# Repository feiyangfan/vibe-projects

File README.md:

# vibe-projects
A collection of vibe-coded apps, utilities, and experiments.

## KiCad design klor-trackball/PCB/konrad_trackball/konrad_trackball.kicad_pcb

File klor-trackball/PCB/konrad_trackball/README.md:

# Konrad Trackball KiCad Derivative

This directory is the editable KiCad source for the KLOR 1.4 MX Konrad right-hand PMW3360 trackball derivative.

## Task 3A baseline

Task 3A creates this project as a non-destructive fork of the stock KLOR 1.4 KiCad project.

Baseline rules:

- Stock source remains under `klor-trackball/klor1.4/PCB/klor1_4/` and must not be edited.
- The derivative project basename is `konrad_trackball`.
- `konrad_trackball.kicad_pcb` and `konrad_trackball.kicad_sch` begin byte-identical to the stock `klor1_4` board and schematic.
- The stock design-rules file and local KLOR symbol/footprint libraries are copied unchanged.
- The only intentional content difference in the baseline project file is `meta.filename`, changed from `klor1_4.kicad_pro` to `konrad_trackball.kicad_pro`.
- Stock Gerbers are intentionally not copied. Fabrication outputs must be regenerated from the completed derivative later.
- No Task 2 electrical changes are implemented in Task 3A. Those begin with Task 3B.

Canonical Task 3 plan and gates are documented in `../../design/task3/README.md`.

## Task 3B schematic contract

Task 3B is complete.

The derivative schematic now owns the frozen Task 2 electrical interface:

- `SW22` and `D22` are removed from the schematic;
- RGB is bypassed logically as `SW13 DOUT → SW14 DIN`;
- U1-side nets are `PMW_SCK`, `PMW_MOSI`, `PMW_MISO`, and `PMW_CS`;
- `J4` is the 1×7 PMW3360/Kivipallur keyboard-side connector:
  `1=PMW_CS, 2=PMW_MISO, 3=PMW_MOSI, 4=PMW_SCK, 5=NC, 6=VCC, 7=GND`;
- `J1.3` is NC and `J1.4/TX` remains the active split connection;
- `J2`, `OLED1`, and `BZ1` are DNP for revision 1.

The PCB remained the stock baseline through Task 3B. Task 3C subsequently synchronized the physical board.

See `../../design/task3/TASK3B_RESULT.md`.

## Task 3C PCB synchronization

Task 3C is complete.

The PCB now matches the authorized destructive portion of the Task 3B contract:

- `SW22` and `D22` are physically removed;
- the deleted-key local matrix copper is removed while `col1` and `row3` remain distinct;
- `RX` is retired and `J1.3` is physically no-net;
- `J1.4/TX` remains intact;
- U1 owns `PMW_SCK`, `PMW_MOSI`, `PMW_MISO`, and `PMW_CS`;
- SW13 DOUT and SW14 DIN are one PCB net with a permanent B.Cu splice;
- J4 exists with the frozen 1×7 keyboard-side pin contract.

Task 3C left J4 staged off-board and kept stock Edge.Cuts unchanged.

See `../../design/task3/TASK3C_RESULT.md`.

## Task 3D connector and pass-through

Task 3D is complete.

- J4 is final-placed on `F.Cu` at `(147.724665,142.367997)`, rotation 0°.
- Its row midpoint is `(147.724665,134.747997)`, +4.613622 mm X from the locked breakout guide center.
- The board has an actual open 2 mm edge notch matching the locked 2×22 mm service envelope.
- A local +X tongue supports the J4 through-holes.
- VCC and the RGB bypass are locally rerouted only where required by the notch/header.
- At the end of Task 3D, J4-to-U1 PMW routing was intentionally incomplete; Task 3E completes it below.

See `../../design/task3/TASK3D_RESULT.md`.

## Task 3E PMW3360 routing

Task 3E is complete.

- `PMW_CS`, `PMW_MISO`, `PMW_MOSI`, and `PMW_SCK` are routed from U1 to J4.
- J4.6 connects to the existing `VCC` rail.
- J4.7 connects to `GND`.
- J4.5 / MOTION remains NC.
- The routing is additive; Task 3D connector/pass-through geometry and all pre-existing copper are preserved.

See `../../design/task3/TASK3E_RESULT.md`.

**Next: Task 3F — preservation and integrated DRC audit.**

## Zone-fill cache policy

Generated `filled_polygon` cache data is not committed. The Task 3E board remains directly accessible through repository tooling. Refill zones in KiCad before DRC/fabrication, then strip cached fills again before committing.

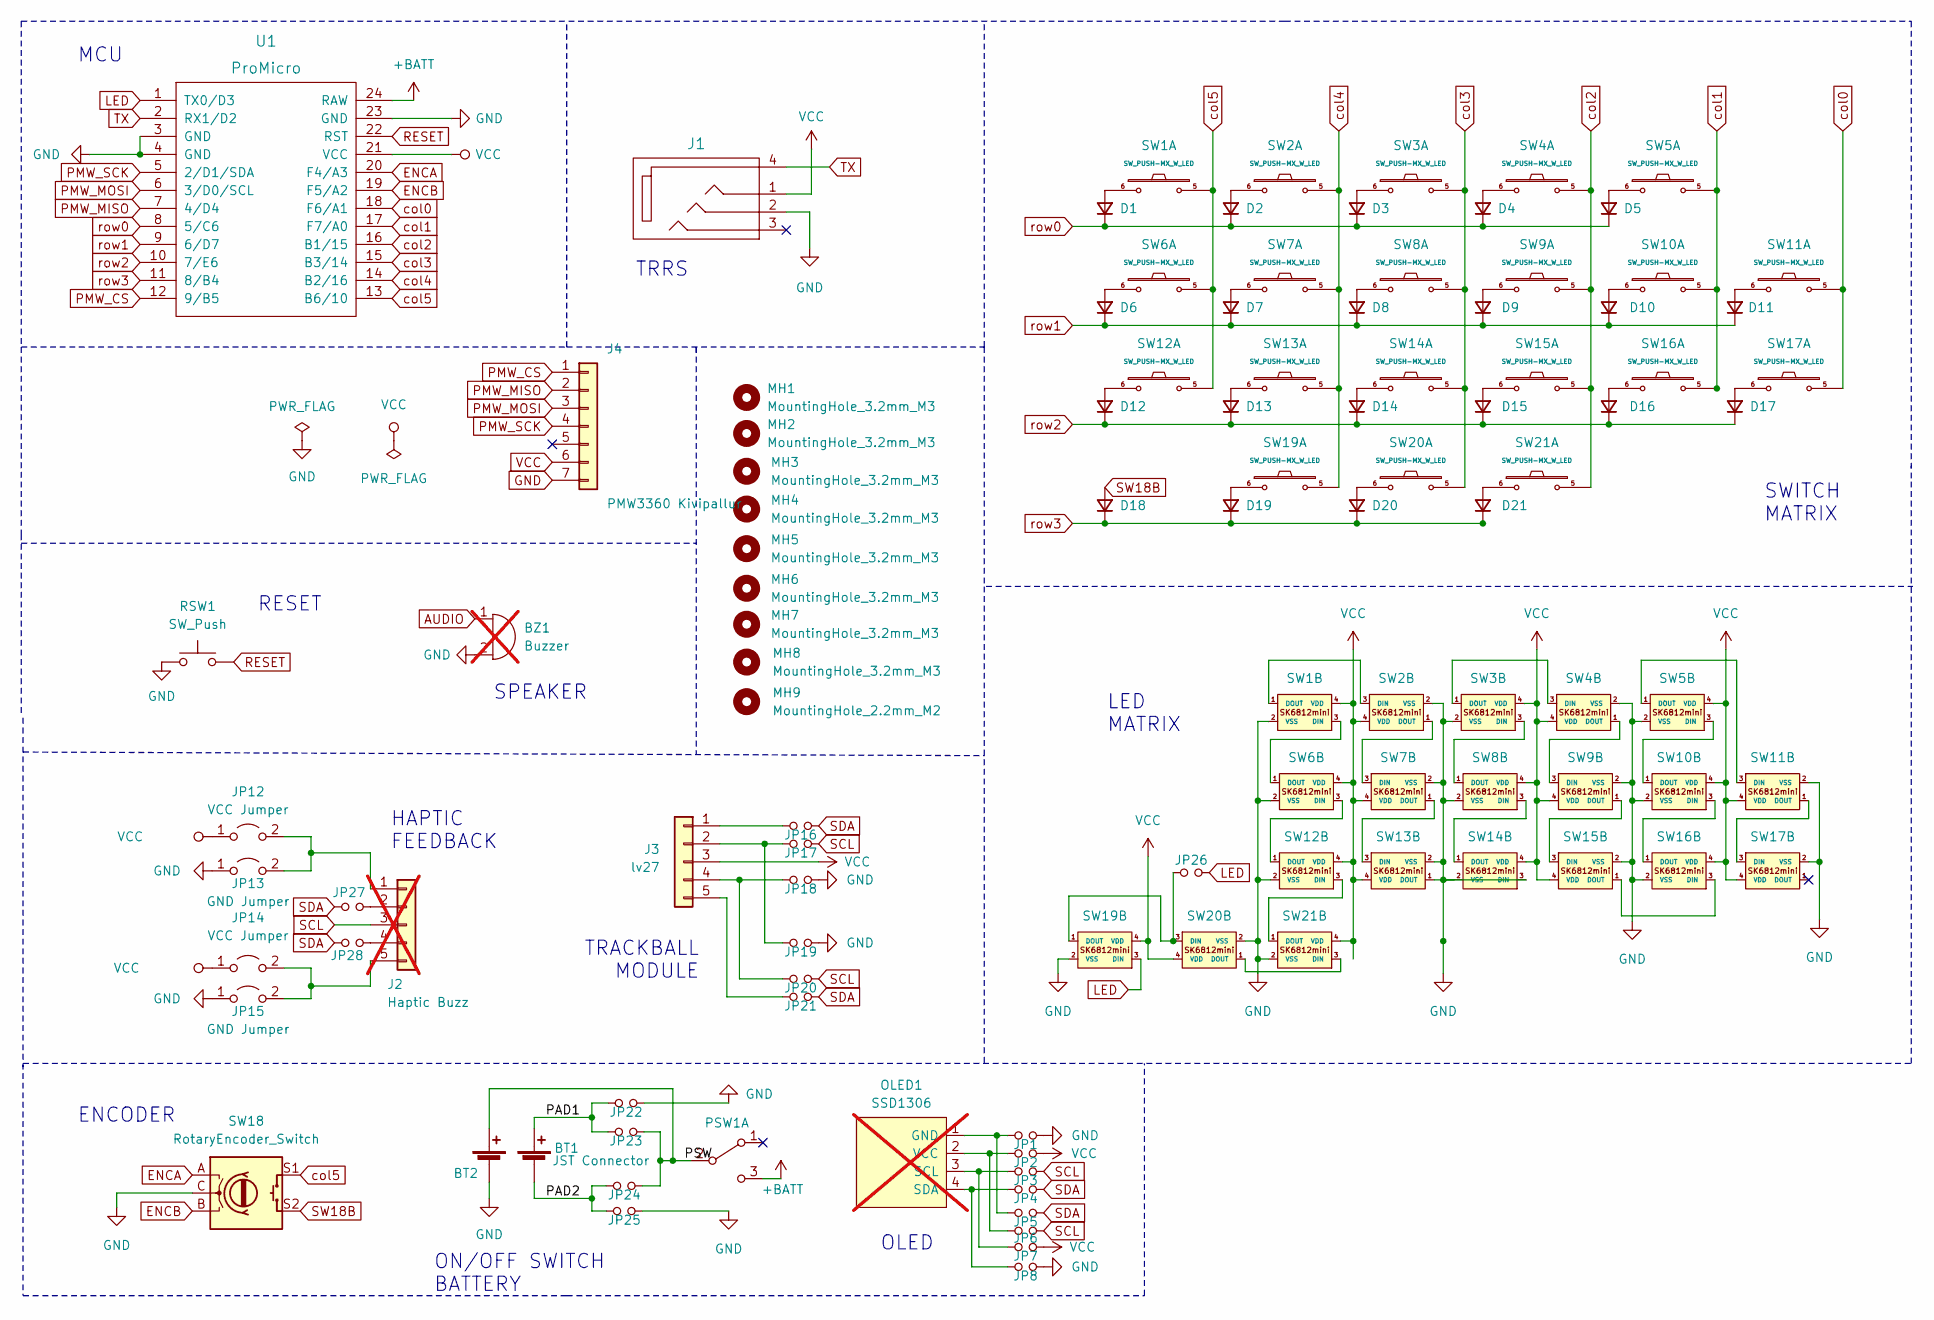
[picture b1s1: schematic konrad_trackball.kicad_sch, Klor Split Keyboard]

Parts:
BT1: JST Connector; JST_PH_reversible
BT2: Battery_Cell; custombatteryconnector_small
BZ1: Buzzer; Buzzer_Mallory_AST1109MLTRQ_reversible; not fitted
D1, D2, D3, D4, D5, D6, D7, D8, D9, D10, D11, D12, D13, D14, D15, D16, D17, D18, D19, D20, D21: D_Small; Diode_SOD123
J1: MJ-4PP-9
J2: Haptic Buzz; Pimoroni Haptic Buzz DRV2605L Driver; not fitted
J3: lv27; lvc27_onlyInput
J4: PMW3360 Kivipallur; PinHeader_1x07_P2.54mm_Vertical
JP1, JP2, JP3, JP4, JP5, JP6, JP7, JP8, JP16, JP17, JP18, JP19, JP20, JP21, JP22, JP23, JP24, JP25, JP26, JP27, JP28: Device_Jumper_NO_Small; Jumper
JP12, JP14: VCC Jumper; Jumper
JP13, JP15: GND Jumper; Jumper
MH1, MH2, MH3, MH4, MH5, MH6, MH7, MH8: MountingHole_3.2mm_M3
MH9: MountingHole_2.2mm_M2
OLED1: SSD1306; SSD1306_128x64OLED; not fitted
PSW1: SW_DPDT_x2; MSK12C02_reversible
RSW1: SW_Push; SW_Push_1P1T-MP_NO_Horizontal_Alps_SKRTLAE010_both_sides
SW1, SW2, SW3, SW4, SW5, SW6, SW7, SW8, SW9, SW10, SW11, SW12, SW13, SW14, SW15, SW16, SW17, SW19, SW20, SW21: SW_PUSH-MX_W_LED; SK6812MINI_and_cherry_1
SW18: RotaryEncoder_Switch; RotaryEncoder_Alps_EC11E-Switch_Vertical_H20mm-keebio_modif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
U1: ProMicro

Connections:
+BATT: PSW1.3 (C), U1.24 (RAW)
/PAD1: BT1.1 (+), JP22.1, JP23.1
/PAD2: BT1.2 (-), JP24.1, JP25.1
/PSW: BT2.1 (+), JP23.2, JP24.2, PSW1.2 (B)
AUDIO: BZ1.1 (-)
ENCA: SW18.A, U1.20 (F4/A3)
ENCB: SW18.B, U1.19 (F5/A2)
LED: JP26.2, SW19.3 (DIN), U1.1 (TX0/D3)
unnamed: D1.2 (A), SW1.6
unnamed: D2.2 (A), SW2.6
unnamed: D3.2 (A), SW3.6
unnamed: D4.2 (A), SW4.6
unnamed: D5.2 (A), SW5.6
unnamed: D6.2 (A), SW6.6
unnamed: D7.2 (A), SW7.6
unnamed: D8.2 (A), SW8.6
unnamed: D9.2 (A), SW9.6
unnamed: D10.2 (A), SW10.6
unnamed: D11.2 (A), SW11.6
unnamed: D12.2 (A), SW12.6
unnamed: D13.2 (A), SW13.6
unnamed: D14.2 (A), SW14.6
unnamed: D15.2 (A), SW15.6
unnamed: D16.2 (A), SW16.6
unnamed: D17.2 (A), SW17.6
unnamed: D19.2 (A), SW19.6
unnamed: D20.2 (A), SW20.6
unnamed: D21.2 (A), SW21.6
unnamed: J2.1, JP12.2 (B), JP13.2 (B)
unnamed: J2.2, JP27.2
unnamed: J2.4, JP28.2
unnamed: J2.5, JP14.2 (B), JP15.2 (B)
unnamed: J3.1, JP16.1
unnamed: J3.2, JP17.1, JP19.1
unnamed: J3.4, JP18.1, JP20.1
unnamed: J3.5, JP21.1
unnamed: JP1.1, JP5.1, OLED1.1 (GND)
unnamed: JP3.1, JP7.1, OLED1.3 (SCL)
unnamed: JP4.1, JP8.1, OLED1.4 (SDA)
unnamed: JP2.1, JP6.1, OLED1.2 (VCC)
unnamed: SW1.3 (DIN), SW6.1 (DOUT)
unnamed: SW1.1 (DOUT), SW2.3 (DIN)
unnamed: SW2.1 (DOUT), SW7.3 (DIN)
unnamed: SW3.3 (DIN), SW8.1 (DOUT)
unnamed: SW3.1 (DOUT), SW4.3 (DIN)
unnamed: SW4.1 (DOUT), SW9.3 (DIN)
unnamed: SW10.3 (DIN), SW16.1 (DOUT)
unnamed: SW5.3 (DIN), SW10.1 (DOUT)
unnamed: SW5.1 (DOUT), SW11.3 (DIN)
unnamed: SW11.1 (DOUT), SW17.3 (DIN)
unnamed: SW12.3 (DIN), SW21.1 (DOUT)
unnamed: SW6.3 (DIN), SW12.1 (DOUT)
unnamed: SW7.1 (DOUT), SW13.3 (DIN)
unnamed: SW8.3 (DIN), SW14.1 (DOUT)
unnamed: SW9.1 (DOUT), SW15.3 (DIN)
unnamed: SW15.1 (DOUT), SW16.3 (DIN)
unnamed: JP26.1, SW19.1 (DOUT), SW20.3 (DIN)
unnamed: SW20.1 (DOUT), SW21.3 (DIN)
PMW_CS: J4.1, U1.12 (9/B5)
PMW_MISO: J4.2, U1.7 (4/D4)
PMW_MOSI: J4.3, U1.6 (3/D0/SCL)
PMW_SCK: J4.4, U1.5 (2/D1/SDA)
RESET: RSW1.2, U1.22 (RST)
SCL: J2.3, JP3.2, JP6.2, JP17.2, JP20.2
SDA: JP4.2, JP5.2, JP16.2, JP21.2, JP27.1, JP28.1
SW18B: D18.2 (A), SW18.S2
TX: J1.4, U1.2 (RX1/D2)
VCC: J1.1, J3.3, J4.6, JP2.2, JP7.2, JP12.1 (A), JP14.1 (A), SW1.4 (VDD), SW2.4 (VDD), SW3.4 (VDD), SW4.4 (VDD), SW5.4 (VDD), SW6.4 (VDD), SW7.4 (VDD), SW8.4 (VDD), SW9.4 (VDD), SW10.4 (VDD), SW11.4 (VDD), SW12.4 (VDD), SW13.4 (VDD), SW14.4 (VDD), SW15.4 (VDD), SW16.4 (VDD), SW17.4 (VDD), SW19.4 (VDD), SW20.4 (VDD), SW21.4 (VDD), U1.21 (VCC)
col0: SW11.5, SW17.5, U1.18 (F6/A1)
col1: SW5.5, SW10.5, SW16.5, U1.17 (F7/A0)
col2: SW4.5, SW9.5, SW15.5, SW21.5, U1.16 (B1/15)
col3: SW3.5, SW8.5, SW14.5, SW20.5, U1.15 (B3/14)
col4: SW2.5, SW7.5, SW13.5, SW19.5, U1.14 (B2/16)
col5: SW1.5, SW6.5, SW12.5, SW18.S1, U1.13 (B6/10)
row0: D1.1 (K), D2.1 (K), D3.1 (K), D4.1 (K), D5.1 (K), U1.8 (5/C6)
row1: D6.1 (K), D7.1 (K), D8.1 (K), D9.1 (K), D10.1 (K), D11.1 (K), U1.9 (6/D7)
row2: D12.1 (K), D13.1 (K), D14.1 (K), D15.1 (K), D16.1 (K), D17.1 (K), U1.10 (7/E6)
row3: D18.1 (K), D19.1 (K), D20.1 (K), D21.1 (K), U1.11 (8/B4)

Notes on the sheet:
SWITCH MATRIX
MCU
ON/OFF SWITCH BATTERY
HAPTIC FEEDBACK
ENCODER
OLED
LED MATRIX
TRRS
TRACKBALL MODULE
RESET
SPEAKER

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
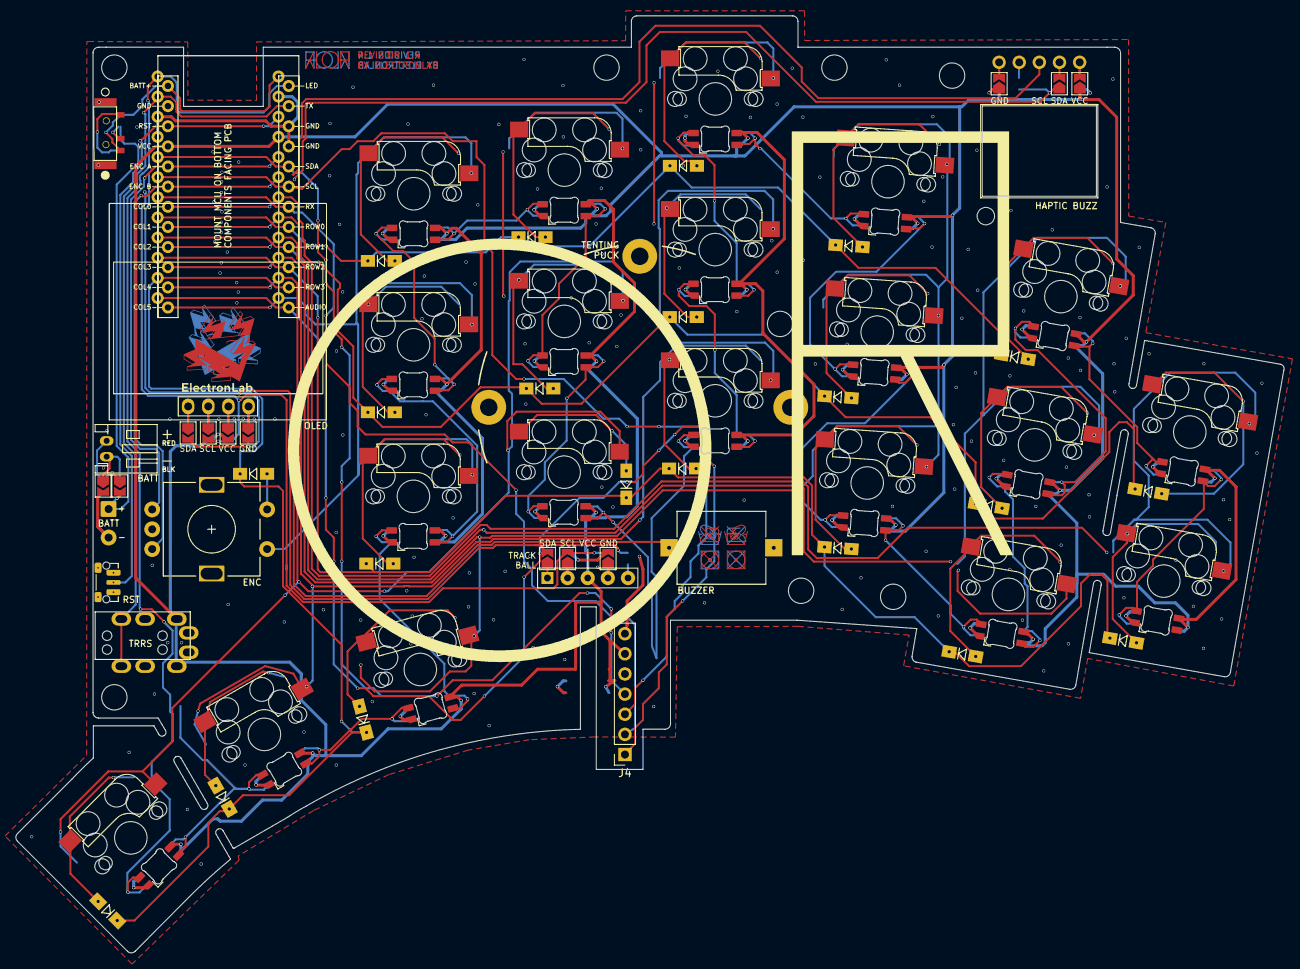
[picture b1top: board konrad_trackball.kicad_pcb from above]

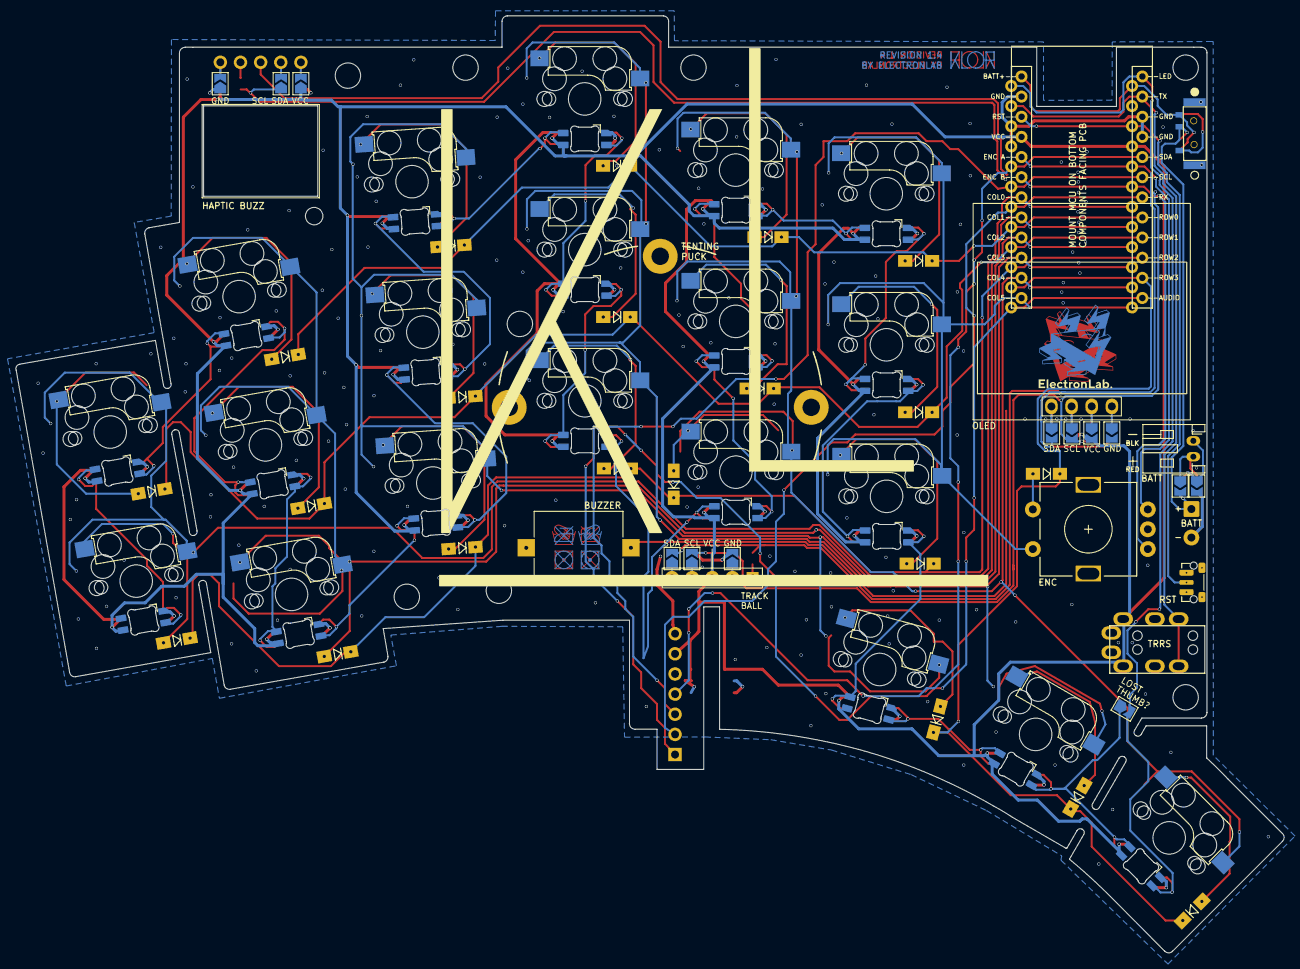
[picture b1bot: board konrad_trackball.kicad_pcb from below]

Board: 2 copper layers, 160.0 x 118.2 mm, 87 parts (14 on the bottom side), 79 nets.

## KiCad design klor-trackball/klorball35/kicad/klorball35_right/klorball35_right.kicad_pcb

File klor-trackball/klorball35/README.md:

# KLORBALL35

<picture>
  <source media="(prefers-color-scheme: dark)" srcset="/docs/images/klorball35-layout-dark.svg">
  <source media="(prefers-color-scheme: light)" srcset="/docs/images/klorball35-layout-light.svg">
  
</picture>

**Klorball35** is a 35-key, column-staggered, low-profile split keyboard with an integrated optical trackball. It's derived from [KLOR](https://github.com/GEIGEIGEIST/KLOR) and [Keyball](https://github.com/Yowkees/keyball),  built with [Kivipallur](https://github.com/dr3san/Kivipallur) as a starting point in [Ergogen](https://ergogen.cache.works/), and designed around Kailh Choc V1 switches, an [0xCB Helios](https://github.com/0xCB-dev/0xCB-Helios) (RP2040) controller per half, and a PixArt **PMW3360** sensor on the right hand.

***

## LAYOUT

Each half carries a 5-column × 3-row main matrix plus a 3-key (left) and 2-key (right)thumb cluster. The right hand gives up one key to make room for the trackball, so the two halves are **18 (left) + 17 (right) = 35 keys**.

- Column-staggered, splayed columns with per-column stagger/splay tuning
- Kailh Choc V1 (low-profile) switches, 18 × 17 mm spacing
- TRRS jack for the inter-half connection
- M2 mounting holes and a matching FR4 switchplate per half
- PMW3360 optical trackball on the right half via the *Kivipallur* breakout

***

## IMAGES

▲ The assembled Klorball35.

▲ Mounted on a tripod.

▲ The right-half trackball assembly.

***

## PCB

[`kicad/`](/kicad/) holds the KiCad 9 projects:

| Project | Description |
| --- | --- |
| [`klorball35_left`](/kicad/klorball35_left/) | Left-half PCB + schematic |
| [`klorball35_right`](/kicad/klorball35_right/) | Right-half PCB + schematic (trackball) |
| [`klorball35_plate_left`](/kicad/klorball35_plate_left/) | Left FR4 switchplate |
| [`klorball35_plate_right`](/kicad/klorball35_plate_right/) | Right FR4 switchplate |
| [`Kivipallur_PMW3360_breakout`](/kicad/Kivipallur_PMW3360_breakout/) | PMW3360 trackball sensor breakout |

Shared footprint and symbol libraries (`Keebio-Parts.pretty`, `keyswitches.pretty`, `Helios.pretty`, `Mounting_Hole.pretty`, etc.) live alongside the projects.

Manufacturing **Gerbers** are in [`gerbers/`](/gerbers/):

- `GERBER-klorball35_left.zip` / `GERBER-klorball35_right.zip` — main PCBs
- `GERBER-klorball35_plate_left.zip` / `GERBER-klorball35_plate_right.zip` — FR4 switchplates
- `GERBER-Kivipallur_PMW3360_breakout.zip` (+ BOM and CPL CSVs) — trackball breakout

***

## SOURCE

The whole board is generated from a single Ergogen definition, [`config.yml`](/config.yml) (Ergogen `4.2.1`). Regenerate the outlines and PCB scaffolds with:

```sh
ergogen config.yml --svg -o output
```

Outputs land in [`output/`](/output/) (`outlines/` as DXF/SVG and `pcbs/` as KiCad files), which are then finished by hand in KiCad.

***

## SWITCHPLATE

A matching FR4 switchplate is generated for each half (`klorball35_plate_left` / `klorball35_plate_right`, with Gerbers in `gerbers/`). The plate outline is shared with the main board; only the key cutouts and M2 screw holes differ.

***

## TRACKBALL

The right half integrates a PixArt **PMW3360DM-T2QU** optical sensor on the *Kivipallur* breakout ([`kicad/Kivipallur_PMW3360_breakout`](/kicad/Kivipallur_PMW3360_breakout/)). It connects to the right-hand Helios over SPI through the breakout slot in the PCB.

***

## FIRMWARE

Each half runs on an [0xCB Helios](https://github.com/0xCB-dev/0xCB-Helios) RP2040 controller (Pro Micro-compatible footprint), so the board can run **QMK** or **ZMK**. A dedicated Klorball35 firmware config isn't published yet; the stock [KLOR QMK config](https://github.com/GEIGEIGEIST/qmk-config-klor) and [KLOR ZMK config](https://github.com/GEIGEIGEIST/zmk-config-klor) are good starting points, with the matrix and the PMW3360 trackball wired up to match this board.

***

## CREDITS

- **[KLOR](https://github.com/GEIGEIGEIST/KLOR)** by [GEIGEIGEIST](https://github.com/GEIGEIGEIST) — One of the best keyboards I have used.
- **[0xCB Helios](https://github.com/0xCB-dev/0xCB-Helios)** by [0xCB](https://github.com/0xCB-dev) — the RP2040 controller.
- **[Ergogen](https://github.com/ergogen/ergogen)** by [MrZealot](https://github.com/mrzealot) — the keyboard generator.
- **[Kivipallur](https://github.com/dr3san/Kivipallur)** by [dr3san](https://github.com/dr3san) — the board that got this project started.
- **[25mm Trackball Housing](https://www.thingiverse.com/thing:6719828)** by [kepeo](https://www.thingiverse.com/kepeo/designs)
- The **Keebio** footprint library and the PixArt PMW3360 breakout that the Kivipallur design is based on.

Built by **danbowles**.

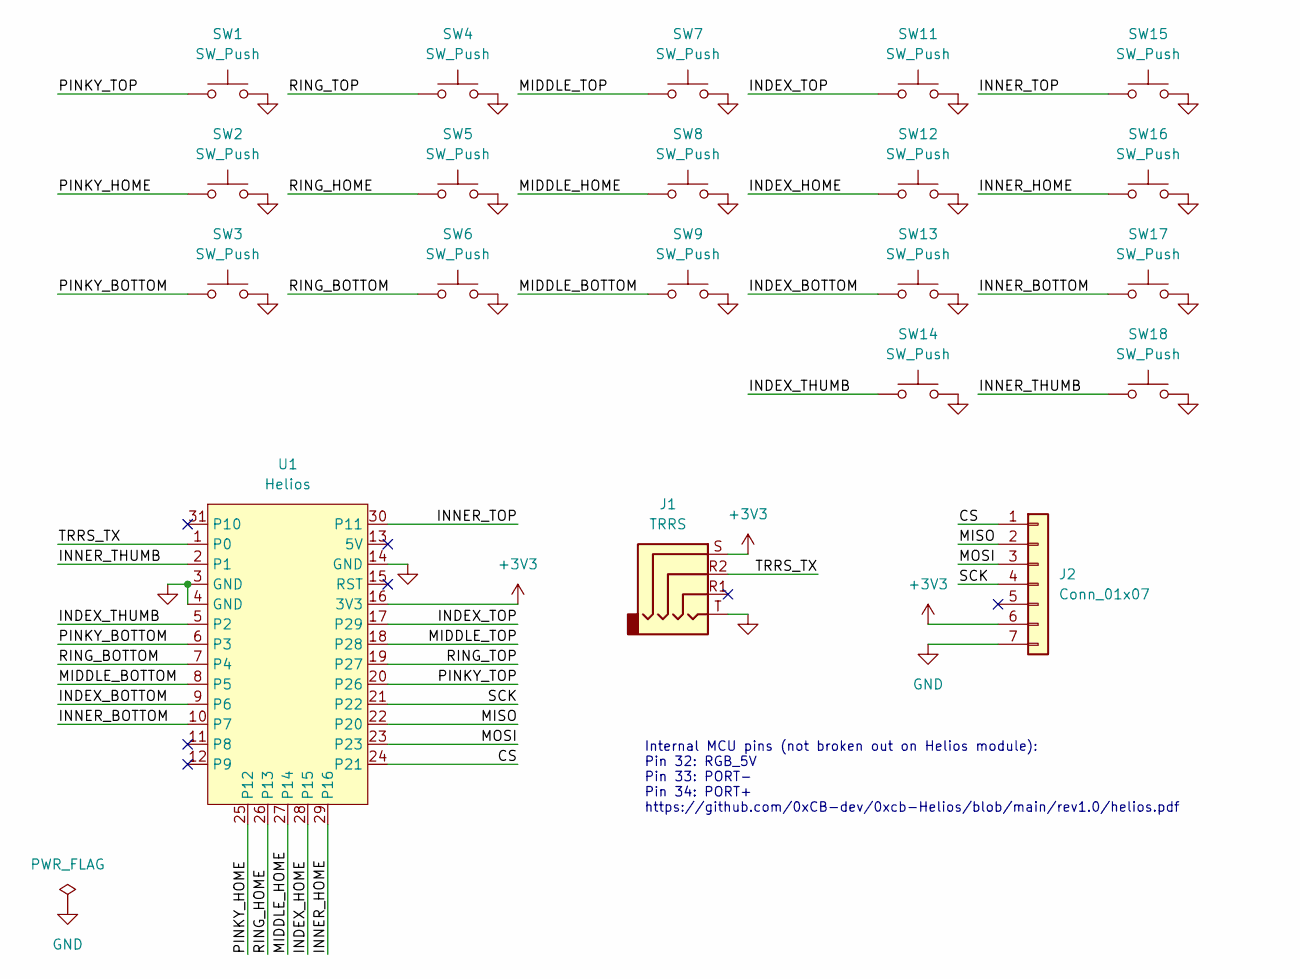
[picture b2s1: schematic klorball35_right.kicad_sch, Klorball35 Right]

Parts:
J1: TRRS; TRRS-PJ-320A
J2: Conn_01x07; PinHeader_1x07_P2.54mm_Vertical
SW1, SW2, SW3, SW4, SW5, SW6, SW7, SW8, SW9, SW11, SW12, SW13, SW14, SW15, SW16, SW17, SW18: SW_Push; Kailh_socket_PG1350_optional
U1: Helios; Helios_ACH

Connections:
+3V3: J1.S, J2.6, U1.16 (3V3)
/CS: J2.1, U1.24 (P21)
/INDEX_BOTTOM: SW13.1, U1.9 (P6)
/INDEX_HOME: SW12.1, U1.28 (P15)
/INDEX_THUMB: SW14.1, U1.5 (P2)
/INDEX_TOP: SW11.1, U1.17 (P29)
/INNER_BOTTOM: SW17.1, U1.10 (P7)
/INNER_HOME: SW16.1, U1.29 (P16)
/INNER_THUMB: SW18.1, U1.2 (P1)
/INNER_TOP: SW15.1, U1.30 (P11)
/MIDDLE_BOTTOM: SW9.1, U1.8 (P5)
/MIDDLE_HOME: SW8.1, U1.27 (P14)
/MIDDLE_TOP: SW7.1, U1.18 (P28)
/MISO: J2.2, U1.22 (P20)
/MOSI: J2.3, U1.23
/PINKY_BOTTOM: SW3.1, U1.6 (P3)
/PINKY_HOME: SW2.1, U1.25 (P12)
/PINKY_TOP: SW1.1, U1.20 (P26)
/RING_BOTTOM: SW6.1, U1.7 (P4)
/RING_HOME: SW5.1, U1.26 (P13)
/RING_TOP: SW4.1, U1.19 (P27)
/SCK: J2.4, U1.21 (P22)
/TRRS_TX: J1.R2, U1.1 (P0)
GND: J1.T, J2.7, SW1.2, SW2.2, SW3.2, SW4.2, SW5.2, SW6.2, SW7.2, SW8.2, SW9.2, SW11.2, SW12.2, SW13.2, SW14.2, SW15.2, SW16.2, SW17.2, SW18.2, U1.3 (GND), U1.4 (GND), U1.14 (GND)

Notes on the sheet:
Internal MCU pins (not broken out on Helios module): Pin 32: RGB_5V Pin 33: PORT- Pin 34: PORT+ https://github.com/0xCB-dev/0xcb-Helios/blob/main/rev1.0/helios.pdf

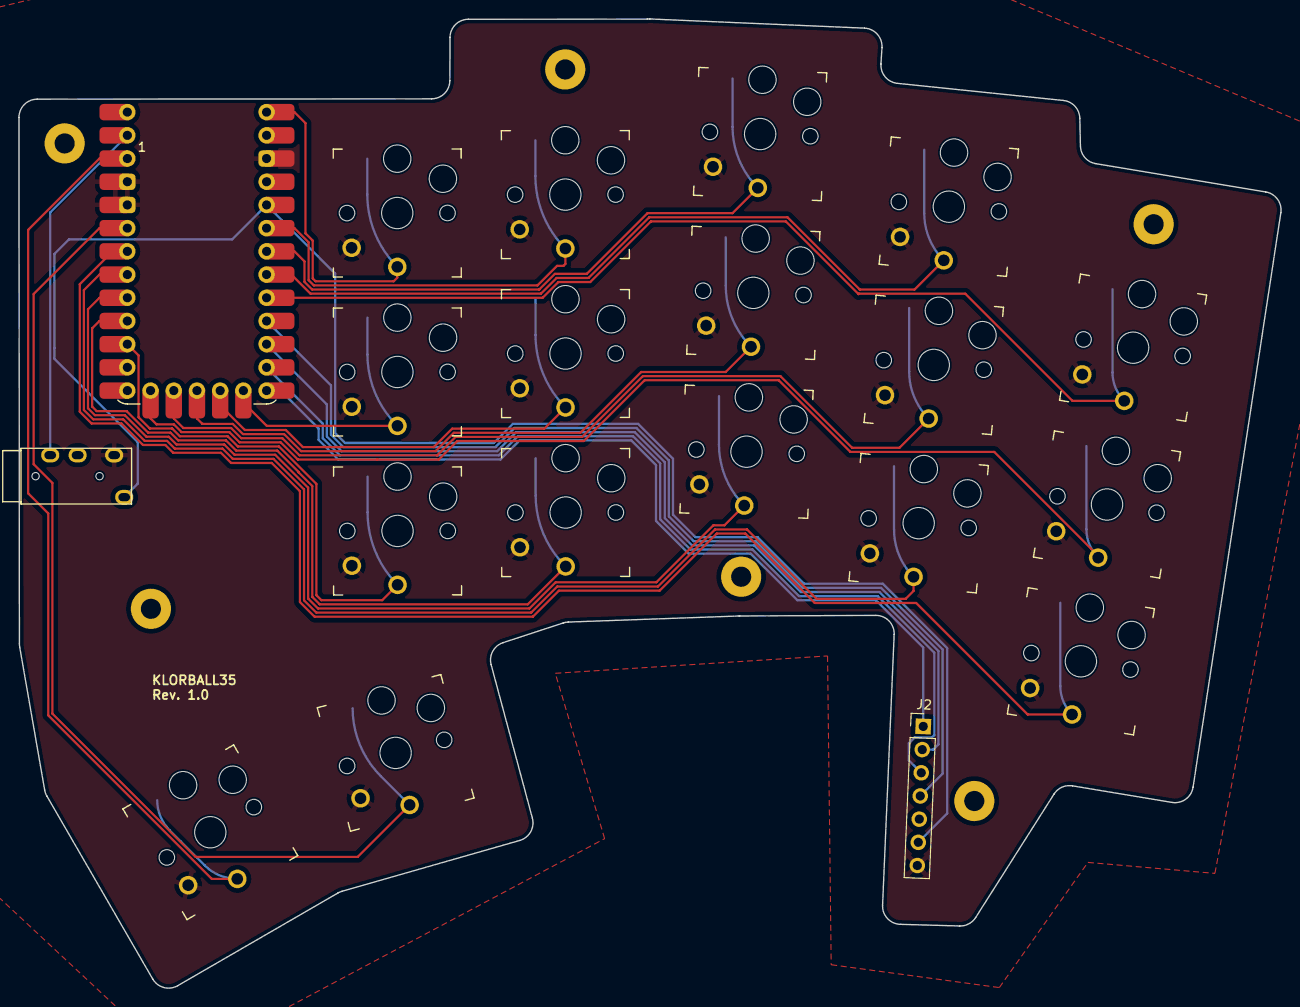
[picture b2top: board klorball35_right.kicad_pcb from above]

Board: 2 copper layers, 138.1 x 106.1 mm, 26 parts (0 on the bottom side), 24 nets.

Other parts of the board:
H7, H7#2, H7#3, H7#4, H7#5, H7#6: MountingHole; MountingHole_2.2mm_M2_Pad

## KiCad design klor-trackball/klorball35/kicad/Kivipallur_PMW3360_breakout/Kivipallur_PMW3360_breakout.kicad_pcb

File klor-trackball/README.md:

# KLOR Trackball — Parametric Ergogen Migration

## Product goal

Build a **fabrication-ready KLOR 1.4 MX / Konrad split keyboard variant with a 25 mm PMW3360 trackball integrated into the right thumb area**, while preserving the KLOR characteristics we intentionally keep and making the modified design reproducible and easy to adjust.

The intended product direction is:

- base keyboard: **KLOR 1.4, MX/full-height, Konrad layout**;
- trackball: **25 mm**, on the right half;
- sensor: **PMW3360**;
- breakout architecture: **Kivipallur-style PMW3360 breakout**;
- housing reference: **Keyball 25 mm Trackball Case Type C**;
- left rotary encoder retained;
- right-thumb architecture: **retain R32/R33, remove R34**;
- right rotary encoder retained in the stock location;
- **39 keys total — 20 left / 19 right**;
- complete deliverable: **PCB + switchplate + case + firmware + fabrication outputs**.

Those details are now frozen for Rev 1 in [`REQUIREMENTS.md`](REQUIREMENTS.md). Task 1 explicitly classified stock KLOR features as required, optional/deferred, or intentionally removed.

## Engineering goal

Ergogen is not the product goal. It is the mechanism used to prevent the project from becoming a collection of difficult manual KiCad and CAD edits.

A meaningful design change should primarily be:

```text
change parameters
    ↓
regenerate
    ↓
validate
```

rather than:

```text
edit KiCad objects
    ↓
repair traces / outlines / UUID-dependent scripts
    ↓
manually synchronize CAD
    ↓
audit unrelated geometry
```

The target architecture is:

```text
canonical design parameters
          ↓
       Ergogen
          ↓
 shared 2D geometry + PCB placement intent
   ┌──────────┼──────────────┐
   ↓          ↓              ↓
  PCB      switchplate    CAD inputs
   ↓          ↓              ↓
 KiCad      DXF/STEP     parametric case
   └──────────┼──────────────┘
              ↓
         validation
              ↓
         fabrication
```

Generated KiCad geometry is a derivative, not the primary geometric source of truth. Avoid UUID-based or object-identity-based KiCad mutation unless an upstream representation is genuinely impossible.

## Core project principles

1. **One geometric authority.** Geometry shared by PCB, switchplate, case, and trackball interfaces should be derived from the same upstream model.
2. **Parameters over copied coordinates.** Relationships such as trackball position, housing screw pattern, breakout offset, and key geometry should be expressed parametrically wherever practical.
3. **Generated output is disposable.** A clean checkout should be able to reproduce generated geometry.
4. **Reference is not authority.** Stock KLOR, Klorball35, and the retired Task-3E board are evidence and comparison targets, not implementation constraints.
5. **No hidden manual geometry.** Any unavoidable downstream manual operation must be documented and reproducible.
6. **Validate numerically.** Visual similarity is not sufficient for preserved layout geometry, mounting axes, PCB interfaces, or mechanical clearances.
7. **A working file is not enough.** A task is complete only when its result can be reproduced from upstream source without substantial repeated manual work.

---

## Reference sources

### KLOR 1.4

`klor1.4/` is the stock KLOR 1.4 reference and should remain unmodified as upstream evidence.

It provides the reference MX/Konrad PCB, firmware, case, switchplate, fabrication constraints, component placement, and structural interfaces.

### Klorball35 / Kivipallur

`klorball35/` is a design reference, not the target keyboard.

It demonstrates an Ergogen-driven split-keyboard workflow plus a PMW3360/Kivipallur trackball architecture, but it uses different key geometry, Choc switches, and a different overall layout.

Useful concepts should be reused; its geometry should not be copied wholesale.

### Trackball housing

`Keyball 25mm Trackball Case Type C - 6719828/` contains the housing STEP/STL reference used for the 25 mm trackball mechanical interface.

### Retired implementation

The previous implementation reached a routed Task 3E KiCad derivative using direct KiCad mutation and preservation scripts.

That implementation is intentionally retired from the active working tree, but remains recoverable from Git:

- pre-migration commit: `432ea630584c22dff2e9f5a596138dcc7602013f`;
- previous Task-3E PCB blob: `cdc63c3081881861bdcba8f0c6bc03a5b242baed`;
- summarized regression evidence: `ergogen/reference-baseline.yaml`.

The old implementation is useful for comparison and recovered engineering evidence. It should not dictate the architecture of the new design.

---

# Sequential roadmap

The dependency order is:

```text
Task 0  generation feasibility
   ↓
Task 1  product requirements
   ↓
Task 2  canonical geometry
   ↓
Task 3  electrical PCB generation
   ↓
Task 4  regeneration-safe routing
   ↓
Task 5  parametric switchplate
   ↓
Task 6  parametric right case
   ↓
Task 7  full digital integration
   ↓
Task 8  firmware
   ↓
Task 9  fabrication + hardware bring-up
```

## Task 0 — Prove the generation architecture

**Status: COMPLETE**

Before rebuilding the complete keyboard, prove that the toolchain works end to end on a small, real slice of the design.

The feasibility prototype should include:

- several real KLOR/Konrad switch positions;
- representative stock mounting points;
- MCU/TRRS/encoder reference points;
- trackball and breakout reference datums;
- a generated PCB outline;
- a generated switchplate outline;
- at least one real switch footprint;
- at least one RGB footprint;
- generated KiCad output.

Validation should compare generated coordinates numerically with the stock KLOR source rather than relying on screenshots or visual alignment.

**Completion gate**

- Ergogen runs from a clean checkout.
- Two clean generation passes are deterministic.
- Selected stock KLOR positions match numerically.
- Trackball and breakout reference datums match the intended regression reference.
- A KiCad PCB is generated.
- A plate geometry output is generated.
- The process is simple enough that extending the model is clearly preferable to returning to manual KiCad surgery.

Task 0 proves the **workflow**, not the final production geometry.

---

## Task 1 — Freeze product requirements

**Status: COMPLETE**

Define the finished keyboard independently of decisions made only to accommodate the old patched PCB.

Re-audit:

- stock KLOR 1.4;
- Konrad layout;
- Klorball35/Kivipallur;
- Type-C trackball housing;
- stock firmware;
- fabrication requirements.

Explicitly classify stock functionality as:

- **required**;
- **optional**;
- **intentionally removed**.

This includes:

- fixed versus geometry-dependent product decisions;
- right-thumb/trackball decision criteria;
- right rotary encoder trade-space;
- controller;
- TRRS/split transport;
- RGB;
- OLED;
- haptic;
- audio;
- stock pointing-device support;
- battery/power-switch support;
- tenting-puck support;
- reset switch;
- other reversible-board features.

**Completion gate**

A short authoritative requirements document exists, and any geometry-dependent product decision is explicitly bounded and assigned to Task 2 before Task 3 may begin.

---

## Task 2 — Reconstruct the complete KLOR/Konrad geometry in Ergogen

**Status: COMPLETE — REVISION 6 MESH-VERIFIED**

Task 2 begins with a minimal-change study before full reconstruction. The selected implementation baseline is to remove R34/SW22/D22 only, retain R32/R33 and the right encoder, preserve all structural interfaces, and keep PCB/plate/case changes local to the trackball region. See `ergogen/task2/MINIMAL_CHANGE_STUDY.md`.

Revision 5 is **invalidated**. It inferred housing handedness from the STL filename and selected `type_c_left.stl`, which direct mesh inspection shows puts the ball on the right side of the housing and the access opening on +X/right.

Revision 6 re-evaluates from the previously qualified Revision-4 geometry and restores `keyball_trackball_case_25mm_type_c_right.stl`. The validator now determines handedness from the **actual mesh**, not the filename:

- housing X bounds: approximately `[-9.631, +27.963]` mm relative to the ball, so the ball sits toward the **left side of the housing**;
- ball-rim mesh is sparse on -X and dense on +X (measured -X/+X vertex ratio approximately `0.238`), identifying the **access opening on -X/left**;
- housing bulk and Kivipallur/connector structure extend toward **+X/right/outward**.

The digitally qualified ball center is restored to `(15.5, -31.000147, 1.938015634)` mm with approximately **12.938 mm** exposed above the plate. All 19 retained right keys and all nine PCB holes remain. The board-side PMW 1x7 is again at `(0, -22.022143)` in the reclaimed SW22 area, connected to the breakout by a short seven-conductor cable.

Build the actual canonical geometric model.

Before freezing the final right-half geometry, compare the right-thumb/trackball trade-space. At minimum include the historical R34-only + right-encoder baseline and alternatives that remove additional thumb controls and/or the right encoder if they materially improve trackball reach, clearance, or serviceability.

Task 2 must lock the final retained subset of R32/R33/R34, total key count, and right-encoder decision before Task 3.

Model:

- every retained switch center and rotation;
- thumb cluster;
- encoder;
- MCU;
- TRRS;
- structural mounting holes;
- PCB perimeter;
- switchplate perimeter;
- switch cutouts;
- relevant keepout/envelope geometry;
- trackball center;
- trackball housing screw pattern;
- breakout/service path;
- trackball connector position.

First prove that the Ergogen model reproduces the stock KLOR geometry that should remain unchanged.

Then add the trackball modification.

Prefer relationships such as:

```text
trackball position
housing screw offsets
breakout offset
connector offset
```

over separately maintained absolute coordinates.

**Completion gate**

The generated canonical geometry numerically reproduces all intentionally preserved KLOR/Konrad geometry, expresses the trackball system parametrically, and freezes the final right-thumb key set / key count / right-encoder architecture for Task 3.

---

## Task 3 — Establish production footprints and generate the electrical PCB

**Status: COMPLETE**

Task 3 is split into explicit electrical gates:

```text
3A  electrical architecture          COMPLETE
 ↓
3B  production footprints            COMPLETE
 ↓
3C  left unrouted PCB                COMPLETE
 ↓
3D  right unrouted PCB + PMW Rev 6   COMPLETE
 ↓
3E  cross-board electrical freeze    COMPLETE
 ↓
Task 4 routing                        NEXT
```

The detailed subtask contract is in `ergogen/task3/README.md`.

Turn the geometric model into a real electrical PCB definition.

Implement or validate production footprints for all retained hardware, including as applicable:

- MX hotswap switches;
- SK6812 Mini-E RGB;
- diodes;
- RP2040 / Pro Micro-compatible controller;
- TRRS;
- EC11 encoder;
- reset/power components;
- PMW3360 connector;
- mounting hardware.

Encode the electrical model:

- key matrix;
- RGB chain;
- split transport;
- encoder;
- PMW3360 SPI;
- power;
- removed thumb-key circuit;
- final GPIO ownership.

**Completion gate**

Ergogen generates a complete, electrically coherent **unrouted production-intent PCB** from source.

---

## Task 4 — Build a regeneration-safe routing pipeline

**Status: IN PROGRESS — Task 4C**

Task 4 is split into explicit routing gates:

```text
4A  routing rules + net classes             COMPLETE
 ↓
4B  regeneration-safe routing proof         COMPLETE
 ↓
4C  route left PCB                           NEXT
 ↓
4D  route right PCB excluding PMW
 ↓
4E  route PMW3360 interface
 ↓
4F  pair-level DRC + regeneration freeze
 ↓
Task 5
```

The detailed subtask contract is in `ergogen/task4/README.md`.

This task determines whether the migration actually solves the maintenance problem:

> What happens to routing after the Ergogen configuration changes?

The implementation preference remains:

1. deterministic/generated routing where practical;
2. replayable routing logic based on nets and geometry;
3. constrained downstream KiCad routing only where it can survive or be reproduced after regeneration.

Do not recreate the retired architecture of large scripts that search for exact KiCad UUIDs or object identities.

**Completion gate**

Make at least one meaningful upstream geometric change, regenerate, restore both valid routed PCBs without manually rebuilding the affected routing, pass pair-level DRC/unrouted-net checks, and preserve the frozen Task-2/Task-3 contracts.

---

## Task 5 — Build the parametric switchplate

The switchplate should consume the same canonical geometry as the PCB.

Generate or parametrically construct:

- MX cutouts;
- structural mounting holes;
- housing clearance;
- case-owned trackball mounting-axis references;
- breakout/service opening;
- outer plate perimeter.

Ergogen may own the 2D geometry while another CAD tool owns downstream 3D solids.

The critical rule is:

> Trackball and mounting coordinates must not be independently retyped into CAD.

**Completion gate**

PCB and switchplate mounting/trackball interfaces remain aligned automatically when the shared upstream geometry changes.

---

## Task 6 — Build the parametric right case

Create a reproducible editable right-case derivative.

The stock regular right case is a reference, but the new case workflow must be editable and parameter driven.

Preserve or intentionally reproduce:

- KLOR external/interface geometry that matters;
- structural mounting axes;
- PCB/plate stack-up;
- required wall thickness;
- assembly/service access.

Add:

- trackball housing envelope;
- local shell relief;
- breakout access;
- required connector clearances.

The left case should remain stock unless Task 1 identifies a reason to regenerate it.

**Completion gate**

A change to relevant upstream trackball geometry can propagate into the case without manually relocating the associated relief/interface features.

---

## Task 7 — Full digital integration and validation

Assemble the generated system digitally:

```text
PCB
+ switches
+ encoder
+ controller
+ switchplate
+ right case
+ trackball housing
+ 25 mm ball
+ Kivipallur breakout
```

Validate:

- physical collisions;
- keycap clearances;
- trackball finger access;
- housing clearance;
- mounting screw access;
- breakout insertion/removal path;
- connector accessibility;
- case wall thickness;
- PCB-to-case clearance;
- KiCad DRC;
- unrouted nets;
- RGB chain continuity;
- power and grounding assumptions.

**Completion gate**

The complete mechanical/electrical design is fabrication-ready in the digital model.

---

## Task 8 — Firmware

Implement firmware only after the hardware contract is stable.

Implement:

- final key matrix;
- final RGB count and map;
- encoder;
- split transport;
- PMW3360 SPI;
- right-half pointing-device ownership;
- CPI;
- pointer orientation;
- scrolling behavior;
- optional auto-mouse behavior.

Recommended bring-up order:

```text
matrix
→ split
→ encoder
→ RGB
→ SPI communication
→ PMW3360 motion
→ pointer tuning
```

**Completion gate**

Firmware ownership and pin assignments exactly match the generated PCB, and the complete configuration builds reproducibly.

---

## Task 9 — Fabrication package and first hardware revision

Generate the complete release package from a clean checkout:

- KiCad PCB;
- Gerbers and drills;
- BOM/assembly data where applicable;
- switchplate DXF/STEP/STL or equivalent fabrication outputs;
- case STEP/STL;
- firmware;
- assembly documentation.

Independently inspect fabrication outputs before ordering.

Recommended physical bring-up order:

```text
continuity / shorts
→ power rails
→ controller
→ key matrix
→ split
→ RGB
→ encoder
→ PMW3360
→ final pointer tuning
```

**Completion gate**

Revision 1 hardware is fabricated, assembled, electrically validated, and mechanically validated.

---

## Active workspace

`ergogen/` is the active design workspace.

Expected structure:

```text
ergogen/
  config.yaml
  footprints/
  scripts/
  reference-baseline.yaml
  generated/          # reproducible / ignored
```

Generated output should never become the only place where design intent exists.

## Current work

**Task 4C — route the complete left PCB.**

Task 3 is complete. The left/right pair now has a frozen pair-level electrical contract in `ergogen/task3/task3e-cross-board-freeze.yaml`, enforced by `scripts/validate_task3e.py`. The first Task-3E qualification run regenerated both production-intent PCBs deterministically and passed Tasks 2B/2C/2D plus 3A/3B/3C/3D before passing the cross-board integration gate.

Revision 6 remains the canonical right-half mechanical baseline. The electrical freeze does not move the ball, housing, PMW cable header, retained switches, encoder, controller, TRRS, or mounting axes.

A **physical right-half mock-up remains required before Task 4 routing is treated as production-final**. R33/SW21 is approximately **34.20 mm center-to-center** from the ball. The mock-up must validate natural thumb access through the left-side housing opening, ball motion/retention, cable behavior, fasteners, assembly path, and the **5.462 mm** local case-pod extension.

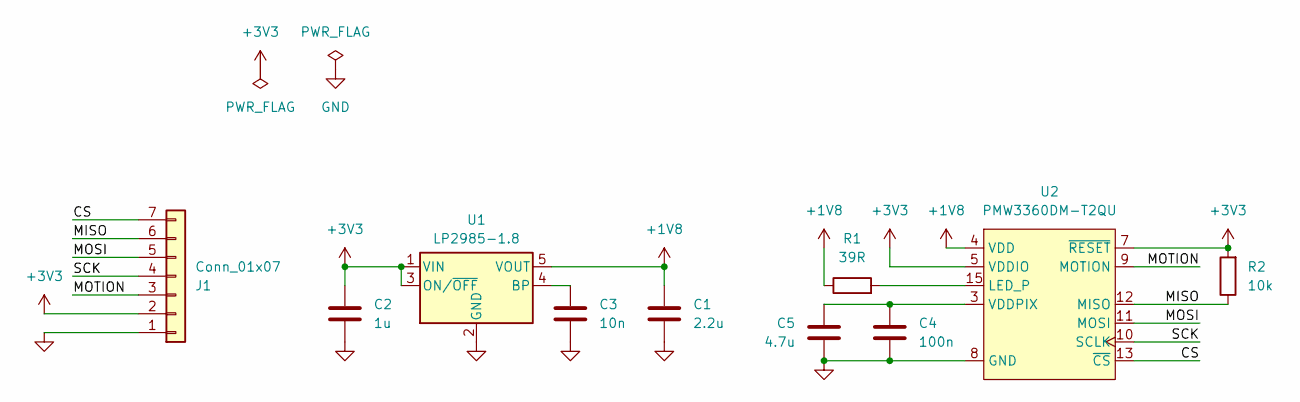
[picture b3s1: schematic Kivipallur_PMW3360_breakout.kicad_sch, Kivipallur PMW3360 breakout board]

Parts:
C1: 2.2u; C_0603_1608Metric_Pad1.08x0.95mm_HandSolder
C2: 1u; C_0603_1608Metric_Pad1.08x0.95mm_HandSolder
C3: 10n; C_0603_1608Metric_Pad1.08x0.95mm_HandSolder
C4: 100n; C_0603_1608Metric_Pad1.08x0.95mm_HandSolder
C5: 4.7u; C_0603_1608Metric_Pad1.08x0.95mm_HandSolder
J1: Conn_01x07; PinHeader_1x07_P2.54mm_Vertical
R1: 39R; R_0603_1608Metric_Pad0.98x0.95mm_HandSolder
R2: 10k; R_0603_1608Metric_Pad0.98x0.95mm_HandSolder
U1: LP2985-1.8; SOT-23-5
U2: PMW3360DM-T2QU; PMW3360DM-T2QU 16Pin

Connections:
+1V8: C1.1, R1.1, U1.5 (VOUT), U2.4 (VDD)
+3V3: C2.1, J1.2, R2.2, U1.1 (VIN), U1.3 (ON/~OFF), U2.5 (VDDIO), U2.7 (~RESET)
/CS: J1.7, U2.13 (~CS)
/MISO: J1.6, R2.1, U2.12 (MISO)
/MOSI: J1.5, U2.11 (MOSI)
/MOTION: J1.3, U2.9 (MOTION)
/SCK: J1.4, U2.10 (SCLK)
GND: C1.2, C2.2, C3.2, C4.1, C5.2, J1.1, U1.2 (GND), U2.8 (GND)
unnamed: C3.1, U1.4 (BP)
unnamed: R1.2, U2.15 (LED_P)
unnamed: C4.2, C5.1, U2.3 (VDDPIX)

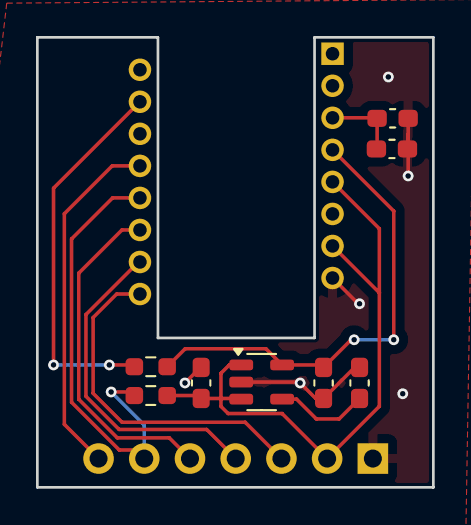
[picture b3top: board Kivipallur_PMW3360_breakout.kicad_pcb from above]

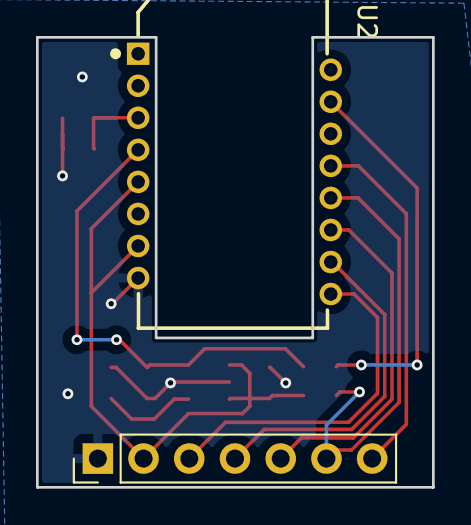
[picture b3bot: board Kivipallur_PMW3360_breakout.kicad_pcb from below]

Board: 2 copper layers, 22.0 x 25.0 mm, 10 parts (2 on the bottom side), 11 nets.

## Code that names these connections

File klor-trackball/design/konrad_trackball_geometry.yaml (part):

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    local_footprint_library_identical_to_stock: true
  schematic_contract:
    connector_reference: J4
    connector_pin_order: {1: PMW_CS, 2: PMW_MISO, 3: PMW_MOSI, 4: PMW_SCK, 5: NC, 6: VCC, 7: GND}
    u1_reassignments: {GP2: PMW_SCK, GP3: PMW_MOSI, GP4: PMW_MISO, GP9: PMW_CS}
    removed_schematic_components: [SW22, D22]
    rgb_bypass: SW13-DOUT-to-SW14-DIN
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pcb_electrical:
  status: task_2_interface_locked
  connector_keyboard_side_order:
    1: {signal: CS, target_net: PMW_CS, gpio: GP9, u1_pad: 12}
    2: {signal: MISO, target_net: PMW_MISO, gpio: GP4, u1_pad: 7}
    3: {signal: MOSI, target_net: PMW_MOSI, gpio: GP3, u1_pad: 6}
    4: {signal: SCK, target_net: PMW_SCK, gpio: GP2, u1_pad: 5}
    5: {signal: MOTION, target_net: NC}
    6: {signal: 3V3, target_net: VCC, u1_pad: 21}
    7: {signal: GND, target_net: GND, u1_pads: [3, 4, 23]}
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    driver: pmw3360
    split_pointing: true
    side: right
    motion_pin: NC
    auto_mouse_revision1: false
  spi:
    driver: SPID0
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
